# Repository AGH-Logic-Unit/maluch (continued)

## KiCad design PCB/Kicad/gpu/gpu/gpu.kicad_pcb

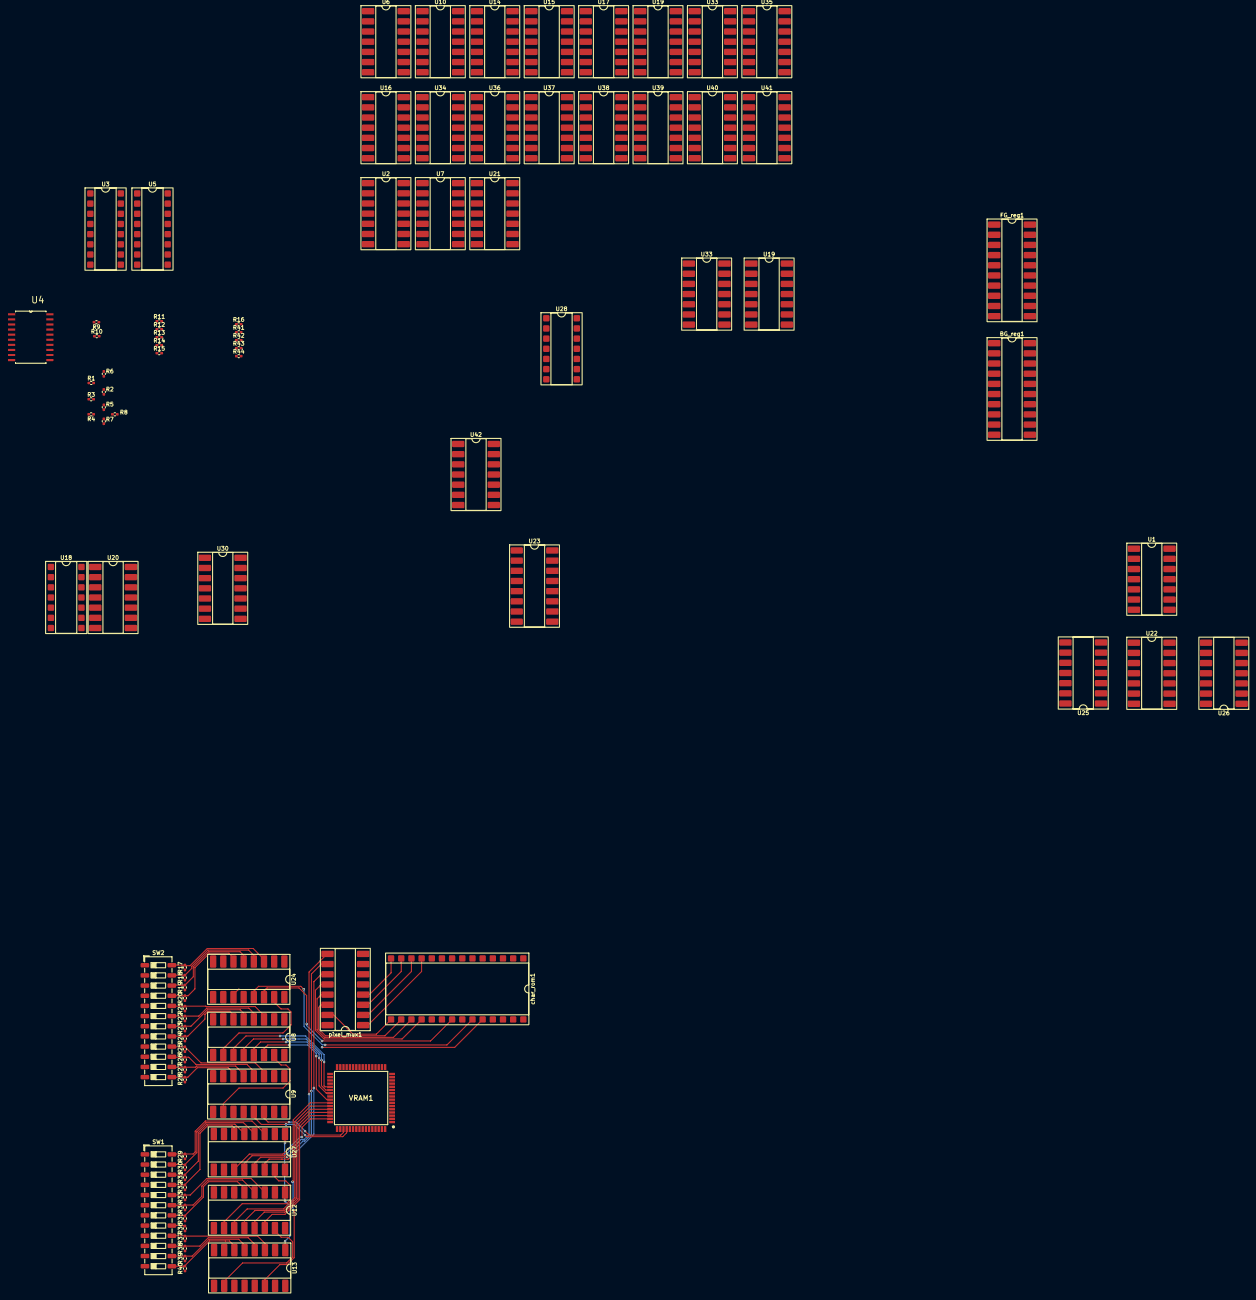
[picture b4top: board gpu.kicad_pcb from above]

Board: 2 copper layers, 91 parts (0 on the bottom side), 188 nets.

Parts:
BG_reg1: 74LS377; DIP-20_W8.89mm_SMDSocket_LongPads
FG_reg1: 74LS377; DIP-20_W8.89mm_SMDSocket_LongPads
R1, R3, R4, R6, R7, R9, R10, R11, R12, R15: 150; R_0402_1005Metric_Pad0.72x0.64mm_HandSolder
R2, R5, R8, R13, R14, R16, R43: 75; R_0402_1005Metric_Pad0.72x0.64mm_HandSolder
R17, R18, R19, R20, R21, R22, R23, R24, R25, R26, R27, R28, R29, R30, R31, R32, R33, R34, R35, R36, R37, R38, R39, R40: 10k; R_0402_1005Metric_Pad0.72x0.64mm_HandSolder
R41: 620; R_0402_1005Metric_Pad0.72x0.64mm_HandSolder
R42: 1k; R_0402_1005Metric_Pad0.72x0.64mm_HandSolder
R44: 390; R_0402_1005Metric_Pad0.72x0.64mm_HandSolder
SW1, SW2: SW_DIP_x12; SW_DIP_SPSTx12_Slide_6.7x32.04mm_W6.73mm_P2.54mm_LowProfile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
U1, U6, U10, U15, U16, U17, U22, U36, U39, U40: 74LS30; DIP-14_W8.89mm_SMDSocket_LongPads
U2, U7, U20, U21, U25, U26: 74LS04; DIP-14_W8.89mm_SMDSocket_LongPads
U3, U5: 74LS157; DIP-16_W7.62mm_SMDSocket_SmallPads
U4: 74HC574D.653; SOIC127P1032X265-20N
U8, U9, U12, U13, U24, U27: 74LS163; DIP-16_W8.89mm_SMDSocket_LongPads
U14, U34: 74LS00; DIP-14_W8.89mm_SMDSocket_LongPads
U18: 74LS08; DIP-14_W7.62mm_SMDSocket_SmallPads
U19, U19#2, U33, U33#2, U35, U37, U38, U41: 74LS32; DIP-14_W8.89mm_SMDSocket_LongPads
U23: 74LS175; DIP-16_W8.89mm_SMDSocket_LongPads
U28: 74LS11; DIP-14_W7.62mm_SMDSocket_SmallPads
U30, U42: 4075; DIP-14_W8.89mm_SMDSocket_LongPads
VRAM1: 71342LA20PFG8; QFP80P1600X1600X160-64N
char_rom1: AT28C64B-15PU; DIP-28_W15.24mm_SMDSocket_SmallPads
pixel_mux1: 74LS151; DIP-16_W8.89mm_SMDSocket_LongPads

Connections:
/HSYNC_OUT: U23.2 (Q0), U28.13
/Hcount0: U27.14 (Q0), pixel_mux1.11 (S0)
/Hcount1: U27.13 (Q1), pixel_mux1.10 (S1)
/Hcount2: U27.12 (Q2), pixel_mux1.9 (S2)
/Hcount3: U27.11 (Q3), VRAM1.47 (A0R)
/Hcount4: U12.14 (Q0), VRAM1.46 (A1R)
/Hcount5: U12.13 (Q1), VRAM1.45 (A2R)
/Hcount6: U12.12 (Q2), VRAM1.44 (A3R)
/Hcount7: U12.11 (Q3), VRAM1.43 (A4R)
/Hcount8: U13.14 (Q0), VRAM1.42 (A5R)
/I/O0: BG_reg1.3 (D0), FG_reg1.3 (D0)
/I/O1: BG_reg1.4 (D1), FG_reg1.4 (D1)
/I/O2: BG_reg1.7 (D2), FG_reg1.7 (D2)
/I/O3: BG_reg1.8 (D3), FG_reg1.8 (D3)
/I/O4: BG_reg1.13 (D4), FG_reg1.13 (D4)
/I/O5: BG_reg1.14 (D5), FG_reg1.14 (D5)
/I/O6: BG_reg1.17 (D6), FG_reg1.17 (D6)
/I/O7: BG_reg1.18 (D7), FG_reg1.18 (D7)
/I/O8: U22.1, U25.3
/I/O9: U1.2, U22.2
/Output/Blue0: R41.1, U4.12 (Q7)
/Output/Blue1: R42.1, U4.13 (Q6)
/Output/Bout: R43.2, R44.2
/Output/Green0: R1.1, U4.16 (Q3)
/Output/Green1: R3.1, U4.15 (Q4)
/Output/Green2: R4.1, U4.14 (Q5)
/Output/PixIn: U3.1 (S), U5.1 (S), pixel_mux1.5 (Z)
/Output/Red0: R9.1, U4.19 (Q0)
/Output/Red1: R10.1, U4.18 (Q1)
/Output/Red2: R11.1, U4.17 (Q2)
/VGA Synchronization/12bit Hcounter/nRST: U12.1 (~MR), U13.1 (~MR), U18.3, U27.1 (~MR)
/VGA Synchronization/12bit Vcounter/DSET0: R17.2, SW2.24, U24.3 (D0)
/VGA Synchronization/12bit Vcounter/DSET1: R18.2, SW2.23, U24.4 (D1)
/VGA Synchronization/12bit Vcounter/DSET2: R19.2, SW2.22, U24.5 (D2)
/VGA Synchronization/12bit Vcounter/DSET3: R20.2, SW2.21, U24.6 (D3)
/VGA Synchronization/12bit Vcounter/DSET4: R21.2, SW2.20, U8.3 (D0)
/VGA Synchronization/12bit Vcounter/DSET5: R22.2, SW2.19, U8.4 (D1)
/VGA Synchronization/12bit Vcounter/DSET6: R23.2, SW2.18, U8.5 (D2)
/VGA Synchronization/12bit Vcounter/DSET7: R24.2, SW2.17, U8.6 (D3)
/VGA Synchronization/12bit Vcounter/DSET8: R25.2, SW2.16, U9.3 (D0)
/VGA Synchronization/12bit Vcounter/DSET9: R26.2, SW2.15, U9.4 (D1)
/VGA Synchronization/12bit Vcounter/DSET10: R27.2, SW2.14, U9.5 (D2)
/VGA Synchronization/12bit Vcounter/DSET11: R28.2, SW2.13, U9.6 (D3)
/VGA Synchronization/12bit Vcounter/EN: U8.7 (CEP), U9.7 (CEP), U18.2, U20.3, U24.7 (CEP), U37.6
/VGA Synchronization/12bit Vcounter/nRST: U8.1 (~MR), U9.1 (~MR), U18.8, U24.1 (~MR)
/VGA Synchronization/HSET0: R29.2, SW1.24, U27.3 (D0)
/VGA Synchronization/HSET1: R30.2, SW1.23, U27.4 (D1)
/VGA Synchronization/HSET2: R31.2, SW1.22, U27.5 (D2)
/VGA Synchronization/HSET3: R32.2, SW1.21, U27.6 (D3)
/VGA Synchronization/HSET4: R33.2, SW1.20, U12.3 (D0)
/VGA Synchronization/HSET5: R34.2, SW1.19, U12.4 (D1)
/VGA Synchronization/HSET6: R35.2, SW1.18, U12.5 (D2)
/VGA Synchronization/HSET7: R36.2, SW1.17, U12.6 (D3)
/VGA Synchronization/HSET8: R37.2, SW1.16, U13.3 (D0)
/VGA Synchronization/HSET9: R38.2, SW1.15, U13.4 (D1)
/VGA Synchronization/HSET10: R39.2, SW1.14, U13.5 (D2)
/VGA Synchronization/HSET11: R40.2, SW1.13, U13.6 (D3)
/VGA Synchronization/HVis: U18.5, U23.7 (Q1), U28.10
/VGA Synchronization/Hctrl/COUNT0: U16.1, U36.1, U39.1, U40.1
/VGA Synchronization/Hctrl/COUNT1: U16.2, U36.2, U39.2, U40.2
/VGA Synchronization/Hctrl/COUNT2: U16.3, U36.3, U39.3, U40.3
/VGA Synchronization/Hctrl/COUNT3: U16.4, U36.4, U39.4, U40.4
/VGA Synchronization/Hctrl/COUNT4: U16.5, U21.1, U40.5
/VGA Synchronization/Hctrl/COUNT5: U21.3, U39.6, U40.6
/VGA Synchronization/Hctrl/COUNT6: U21.5, U39.11, U40.11
/VGA Synchronization/Hctrl/COUNT7: U21.9, U36.12, U39.12
/VGA Synchronization/Hctrl/COUNT8: U21.11, U34.1
/VGA Synchronization/Hctrl/COUNT9: U34.2, U34.5, U34.10, U34.13
/VGA Synchronization/Hctrl/HBeginPulse: U28.1, U37.3, U38.6
/VGA Synchronization/Hctrl/HEndPulse: U20.1, U28.2, U37.8
/VGA Synchronization/Hctrl/HVisEnd: U18.4, U37.11, U41.6
/VGA Synchronization/Hctrl/nCOUNT4: U21.2, U36.5, U39.5
/VGA Synchronization/Hctrl/nCOUNT5: U16.6, U21.4, U36.6
/VGA Synchronization/Hctrl/nCOUNT6: U16.11, U21.6, U36.11
/VGA Synchronization/Hctrl/nCOUNT7: U16.12, U21.8, U40.12
/VGA Synchronization/Hctrl/nCOUNT8: U21.10, U34.4, U34.9, U34.12
/VGA Synchronization/VVis: U18.13, U23.15 (Q3), U28.11
/VGA Synchronization/Vctrl/COUNT0: U6.1, U7.5, U10.1, U17.1
/VGA Synchronization/Vctrl/COUNT1: U6.2, U7.9, U10.2
/VGA Synchronization/Vctrl/COUNT2: U6.3, U7.13, U15.3, U17.3
/VGA Synchronization/Vctrl/COUNT3: U6.4, U7.11, U10.4, U15.4
/VGA Synchronization/Vctrl/COUNT4: U2.1, U6.5
/VGA Synchronization/Vctrl/COUNT5: U2.3, U10.6
/VGA Synchronization/Vctrl/COUNT6: U2.5, U6.11, U10.11
/VGA Synchronization/Vctrl/COUNT7: U2.9, U6.12, U10.12, U17.12
/VGA Synchronization/Vctrl/COUNT8: U2.11, U14.4, U14.9, U14.12
/VGA Synchronization/Vctrl/COUNT9: U2.13, U14.2
/VGA Synchronization/Vctrl/nCOUNT0: U7.6, U15.1
/VGA Synchronization/Vctrl/nCOUNT1: U7.8, U15.2, U17.2
/VGA Synchronization/Vctrl/nCOUNT2: U7.12, U10.3
/VGA Synchronization/Vctrl/nCOUNT3: U7.10, U17.4
/VGA Synchronization/Vctrl/nCOUNT4: U2.2, U10.5, U15.5, U17.5
/VGA Synchronization/Vctrl/nCOUNT5: U2.4, U6.6, U15.6, U17.6
/VGA Synchronization/Vctrl/nCOUNT6: U2.6, U15.11, U17.11
/VGA Synchronization/Vctrl/nCOUNT7: U2.8, U15.12
/VGA Synchronization/Vctrl/nCOUNT8: U2.10, U14.1
/VGA Synchronization/Vctrl/nCOUNT9: U2.12, U14.5, U14.10, U14.13
/VGA Synchronization/Vctrl/nVBeginPulse: U28.3, U33.6, U35.6
/VGA Synchronization/Vctrl/nVEndPulse: U7.1, U28.4, U33.8, U33#2.3
/VGA Synchronization/Vctrl/nVVisEnd: U18.12, U19.6, U33.11
/VGA Synchronization/Vctrl/nVcountEnd: U7.3, U18.10, U33.3, U33#2.6
/VSYNC_OUT: U23.10 (Q2), U28.5
/Vcount0: U24.14 (Q0), char_rom1.21 (A10)
/Vcount1: U24.13 (Q1), char_rom1.23 (A11)
/Vcount2: U24.12 (Q2), char_rom1.24 (A9)
/Vcount3: U24.11 (Q3), char_rom1.25 (A8)
/Vcount4: U8.14 (Q0), VRAM1.41 (A6R)
/Vcount5: U8.13 (Q1), VRAM1.39 (A7R)
/Vcount6: U8.12 (Q2), VRAM1.38 (A8R)
/Vcount7: U8.11 (Q3), VRAM1.37 (A9R)
/Vcount8: U9.14 (Q0), VRAM1.51 (A10R)
/Vcount9: U9.13 (Q1), VRAM1.52 (A11R)
/charRow0: char_rom1.14 (GND), pixel_mux1.4 (I0)
/charRow1: char_rom1.13 (I/O2), pixel_mux1.3 (I1)
/charRow2: char_rom1.12 (I/O1), pixel_mux1.2 (I2)
/charRow3: char_rom1.11 (I/O0), pixel_mux1.1 (I3)
/charRow4: char_rom1.15 (I/O3), pixel_mux1.15 (I4)
/charRow5: char_rom1.16 (I/O4), pixel_mux1.14 (I5)
/charRow6: char_rom1.17 (I/O5), pixel_mux1.13 (I6)
/charRow7: char_rom1.18 (I/O6), pixel_mux1.12 (I7)
/commands/nio8: U1.1, U25.4
/commands/nio10: U1.3, U22.3, U25.6
/commands/nio11: U1.4, U22.4, U25.8
/commands/nio12: U1.5, U22.5, U25.10
/commands/nio13: U1.6, U22.6, U25.12
/commands/nio14: U1.11, U22.11, U26.2
/commands/nio15: U1.12, U22.12, U26.4
/ioCLK: BG_reg1.11 (CP), FG_reg1.11 (CP)
/nRST: U18.1, U18.9, U21.13
/nVis: U3.15 (E), U5.15 (E)
/pCLK: U8.2 (CP), U9.2 (CP), U12.2 (CP), U13.2 (CP), U24.2 (CP), U27.2 (CP)
GND: BG_reg1.10 (GND), FG_reg1.10 (GND), R6.1, R7.2, R12.1, R15.2, R17.1, R18.1, R19.1, R20.1, R21.1, R22.1, R23.1, R24.1, R25.1, R26.1, R27.1, R28.1, R29.1, R30.1, R31.1, R32.1, R33.1, R34.1, R35.1, R36.1, R37.1, R38.1, R39.1, R40.1, U1.7 (GND), U2.7 (GND), U3.8 (GND), U4.1 (~OE), U4.10 (GND), U5.8 (GND), U6.7 (GND), U7.7 (GND), U8.8 (GND), U9.8 (GND), U10.7 (GND), U12.8 (GND), U13.8 (GND), U14.7 (GND), U15.7 (GND), U16.7 (GND), U17.7 (GND), U18.7 (GND), U19.7 (GND), U19#2.7 (GND), U20.7 (GND), U21.7 (GND), U22.7 (GND), U23.8 (GND), U24.8 (GND), U25.7 (GND), U26.7 (GND), U27.8 (GND), U28.7 (GND), U30.7 (VSS), U36.7 (GND), U37.7 (GND), U39.7 (GND), U40.7 (GND), VRAM1.25 (GND), VRAM1.55 (~CER), VRAM1.59 (R/~WL), char_rom1.2 (A12), char_rom1.20 (~CE), char_rom1.22 (~OE), pixel_mux1.7 (~E), pixel_mux1.8 (GND)
unnamed: BG_reg1.1 (~E), U19#2.6
unnamed: FG_reg1.1 (~E), U19#2.3
unnamed: R1.2, R2.2, R6.2
unnamed: R2.1, R3.2, R5.2
unnamed: R4.2, R5.1, R7.1, R8.2
unnamed: R10.2, R13.1, R14.2
unnamed: R11.2, R14.1, R15.1, R16.2
unnamed: R9.2, R12.2, R13.2
unnamed: R41.2, R43.1
unnamed: R42.2, R44.1
unnamed: U1.8, U19#2.2
unnamed: U3.4 (Za), U4.6 (D4)
unnamed: U3.7 (Zb), U4.7 (D5)
unnamed: U3.9 (Zc), U4.8 (D6)
unnamed: U3.12 (Zd), U4.9 (D7)
unnamed: U4.2 (D0), U5.7 (Zb)
unnamed: U4.3 (D1), U5.4 (Za)
unnamed: U4.4 (D2), U5.9 (Zc)
unnamed: U4.5 (D3), U5.12 (Zd)
unnamed: U8.15 (TC), U9.10 (CET)
unnamed: U10.8, U33.9, U33#2.1
unnamed: U12.10 (CET), U27.15 (TC)
unnamed: U12.15 (TC), U13.10 (CET)
unnamed: U14.3, U33.2, U33#2.5
unnamed: U14.6, U33.5, U35.5
unnamed: U14.8, U33.10, U33#2.2
unnamed: U14.11, U19.5, U33.13
unnamed: U15.8, U33.1, U33#2.4
unnamed: U16.8, U37.4
unnamed: U17.8, U33.4, U35.4
unnamed: U18.6, U30.5
unnamed: U18.11, U42.8
unnamed: U19#2.1, U19#2.4, U25.2
unnamed: U19#2.5, U22.8
unnamed: U20.2, U30.1
unnamed: U20.4, U30.3
unnamed: U20.5, U28.8
unnamed: U21.12, U30.2, U30.4, U30.12, U42.2
unnamed: U23.4 (D0), U30.9
unnamed: U23.5 (D1), U30.6
unnamed: U23.12 (D2), U30.10
unnamed: U23.13 (D3), U42.9
unnamed: U8.10 (CET), U24.15 (TC)
unnamed: U28.6, U30.13
unnamed: U28.12, U30.8
unnamed: U7.2, U30.11
unnamed: U6.8, U33.12
unnamed: U34.3, U37.5
unnamed: U34.6, U37.2, U38.5
unnamed: U34.8, U37.10
unnamed: U34.11, U37.13, U41.5
unnamed: U36.8, U37.1, U38.4
unnamed: U37.9, U39.8
unnamed: U37.12, U40.8
unnamed: U7.4, U42.1
VCC: BG_reg1.20 (VCC), FG_reg1.20 (VCC), SW1.1, SW1.2, SW1.3, SW1.4, SW1.5, SW1.6, SW1.7, SW1.8, SW1.9, SW1.10, SW1.11, SW1.12, SW2.1, SW2.2, SW2.3, SW2.4, SW2.5, SW2.6, SW2.7, SW2.8, SW2.9, SW2.10, SW2.11, SW2.12, U1.14 (VCC), U2.14 (VCC), U3.16 (VCC), U4.20 (VCC), U5.16 (VCC), U6.14 (VCC), U7.14 (VCC), U8.9 (~PE), U8.16 (VCC), U9.9 (~PE), U9.16 (VCC), U10.14 (VCC), U12.7 (CEP), U12.9 (~PE), U12.16 (VCC), U13.7 (CEP), U13.9 (~PE), U13.16 (VCC), U14.14 (VCC), U15.14 (VCC), U16.14 (VCC), U17.14 (VCC), U18.14 (VCC), U19.14 (VCC), U19#2.14 (VCC), U20.14 (VCC), U21.14 (VCC), U22.14 (VCC), U23.16 (VCC), U24.9 (~PE), U24.10 (CET), U24.16 (VCC), U25.14 (VCC), U26.14 (VCC), U27.7 (CEP), U27.9 (~PE), U27.10 (CET), U27.16 (VCC), U28.9, U28.14 (VCC), U30.14 (VDD), U36.14 (VCC), U37.14 (VCC), U39.14 (VCC), U40.14 (VCC), VRAM1.1 (~OEL), VRAM1.53 (~SEM_R), VRAM1.54 (R/~WR), VRAM1.57 (VCC), VRAM1.60 (~SEML), char_rom1.27 (~WE), char_rom1.28 (VCC), pixel_mux1.16 (VCC)

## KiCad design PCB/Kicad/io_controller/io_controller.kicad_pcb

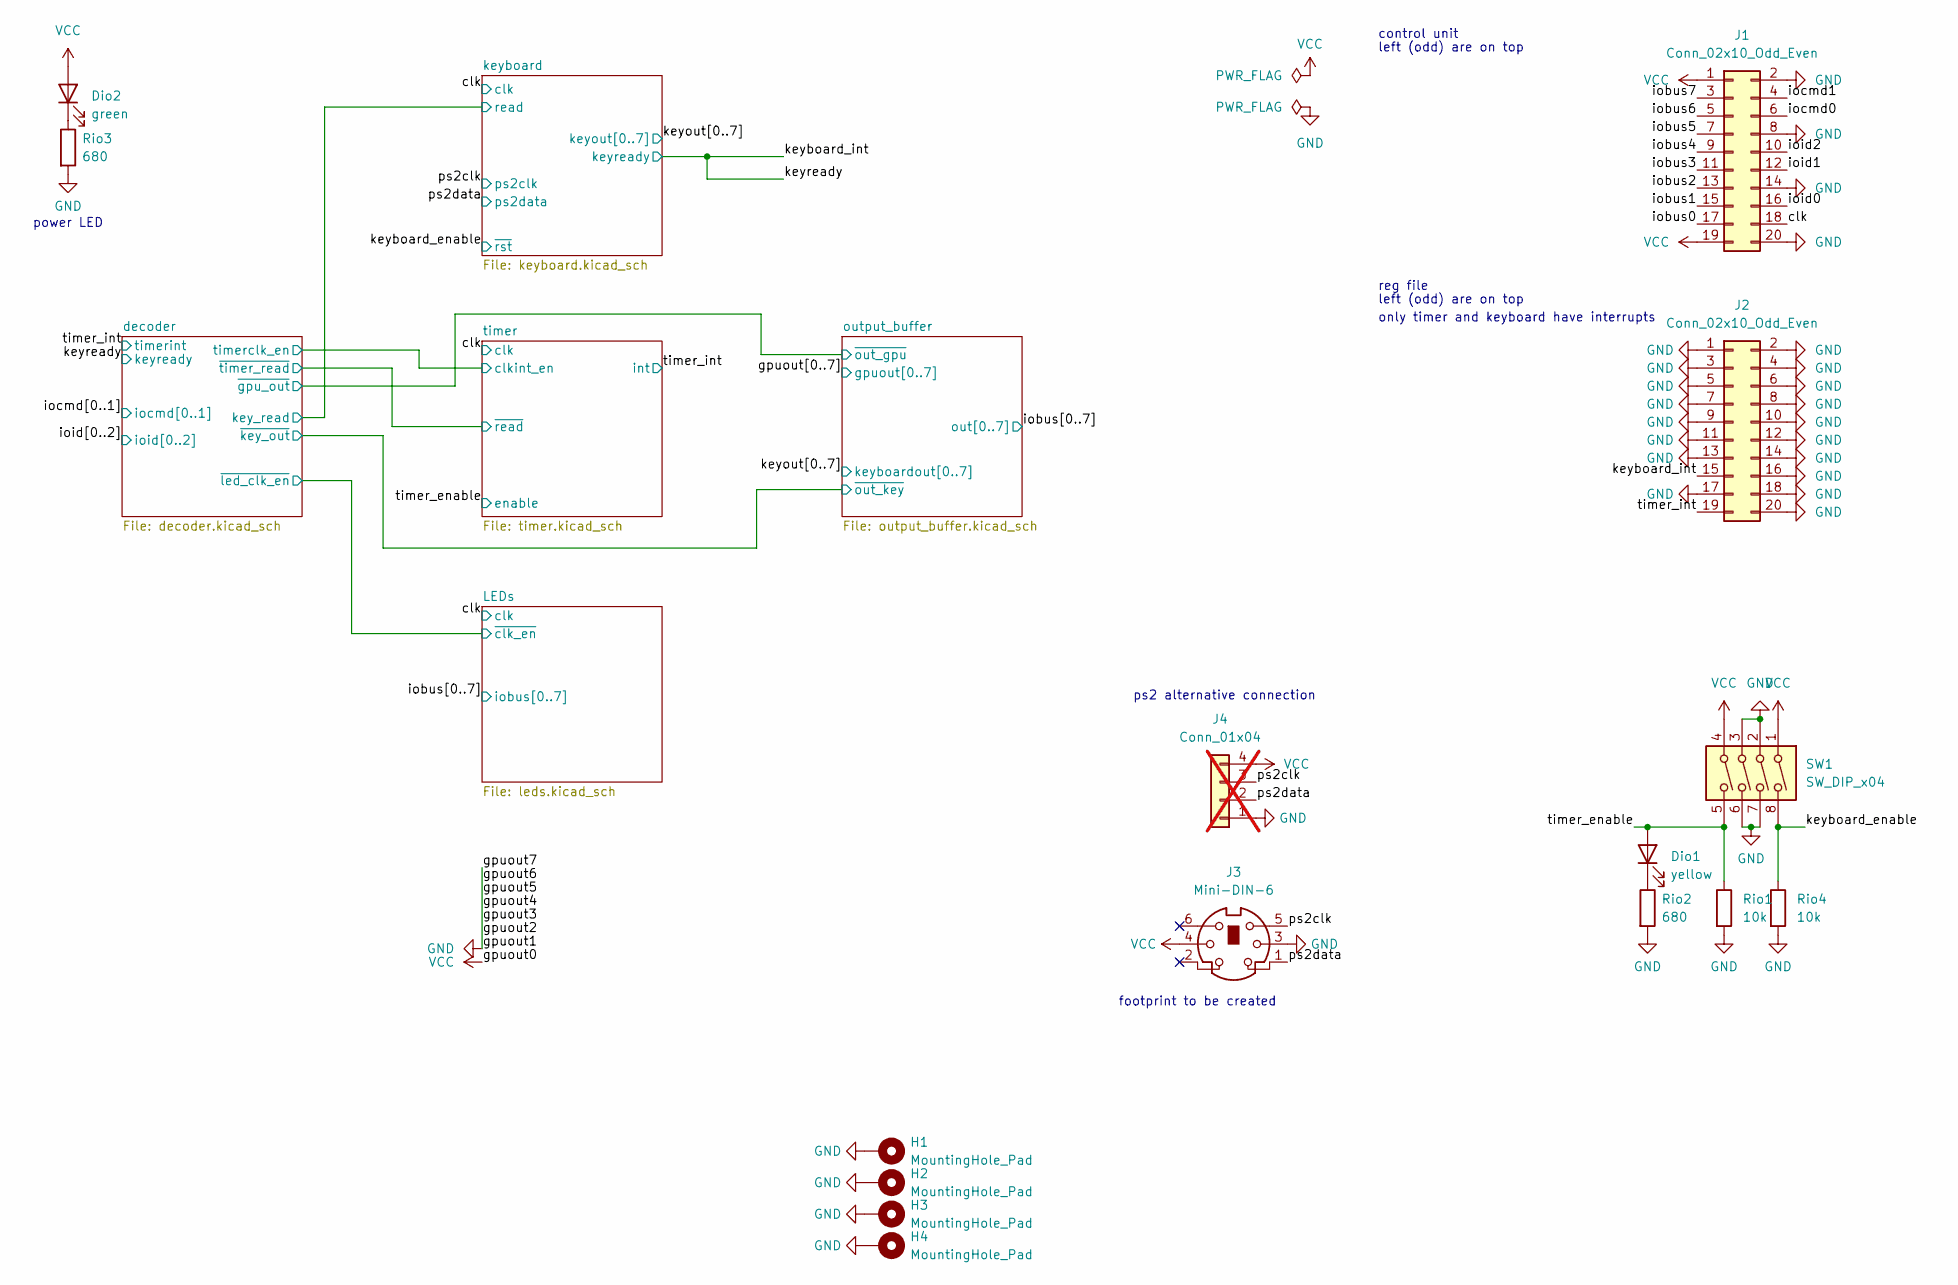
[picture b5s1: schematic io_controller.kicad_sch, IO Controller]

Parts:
Dio1: yellow; D_0603_1608Metric
Dio2: green; D_0603_1608Metric
H1, H2, H3, H4: MountingHole_Pad; MountingHole_2.2mm_M2_DIN965_Pad
J1, J2: Conn_02x10_Odd_Even; PinHeader_2x10_P2.54mm_Horizontal
J3: Mini-DIN-6; MiniDin6_PS2
J4: Conn_01x04; PinHeader_1x04_P2.54mm_Vertical; not fitted
Rio1, Rio4: 10k; R_0402_1005Metric
Rio2, Rio3: 680; R_0402_1005Metric
SW1: SW_DIP_x04; SW_DIP_SPSTx04_Slide_6.7x11.72mm_W7.62mm_P2.54mm_LowProfile

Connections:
/clk: J1.18; also elsewhere on the board
/iobus0: J1.17; also elsewhere on the board
/iobus1: J1.15; also elsewhere on the board
/iobus2: J1.13; also elsewhere on the board
/iobus3: J1.11; also elsewhere on the board
/iobus4: J1.9; also elsewhere on the board
/iobus5: J1.7; also elsewhere on the board
/iobus6: J1.5; also elsewhere on the board
/iobus7: J1.3; also elsewhere on the board
/iocmd0: J1.6; also elsewhere on the board
/iocmd1: J1.4; also elsewhere on the board
/ioid0: J1.16; also elsewhere on the board
/ioid1: J1.12; also elsewhere on the board
/ioid2: J1.10; also elsewhere on the board
/keyboard_enable: Rio4.1, SW1.8; also elsewhere on the board
/keyboard_int: J2.15; also elsewhere on the board
/ps2clk: J3.5, J4.3; also elsewhere on the board
/ps2data: J3.1, J4.2; also elsewhere on the board
/timer_enable: Dio1.2 (A), Rio1.1, SW1.5; also elsewhere on the board
/timer_int: J2.19; also elsewhere on the board
GND: H1.1 (1_1), H2.1 (1_1), H3.1 (1_1), H4.1 (1_1), J1.2, J1.8, J1.14, J1.20, J2.1, J2.2, J2.3, J2.4, J2.5, J2.6, J2.7, J2.8, J2.9, J2.10, J2.11, J2.12, J2.13, J2.14, J2.16, J2.17, J2.18, J2.20, J3.3, J4.1, Rio1.2, Rio2.2, Rio3.2, Rio4.2, SW1.2, SW1.3, SW1.6, SW1.7; also elsewhere on the board
unnamed: Dio1.1 (K), Rio2.1
unnamed: Dio2.1 (K), Rio3.1
VCC: Dio2.2 (A), J1.1, J1.19, J3.4, J4.4, SW1.1, SW1.4; also elsewhere on the board

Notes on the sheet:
left (odd) are on top
power LED
ps2 alternative connection
control unit
reg file
footprint to be created
only timer and keyboard have interrupts

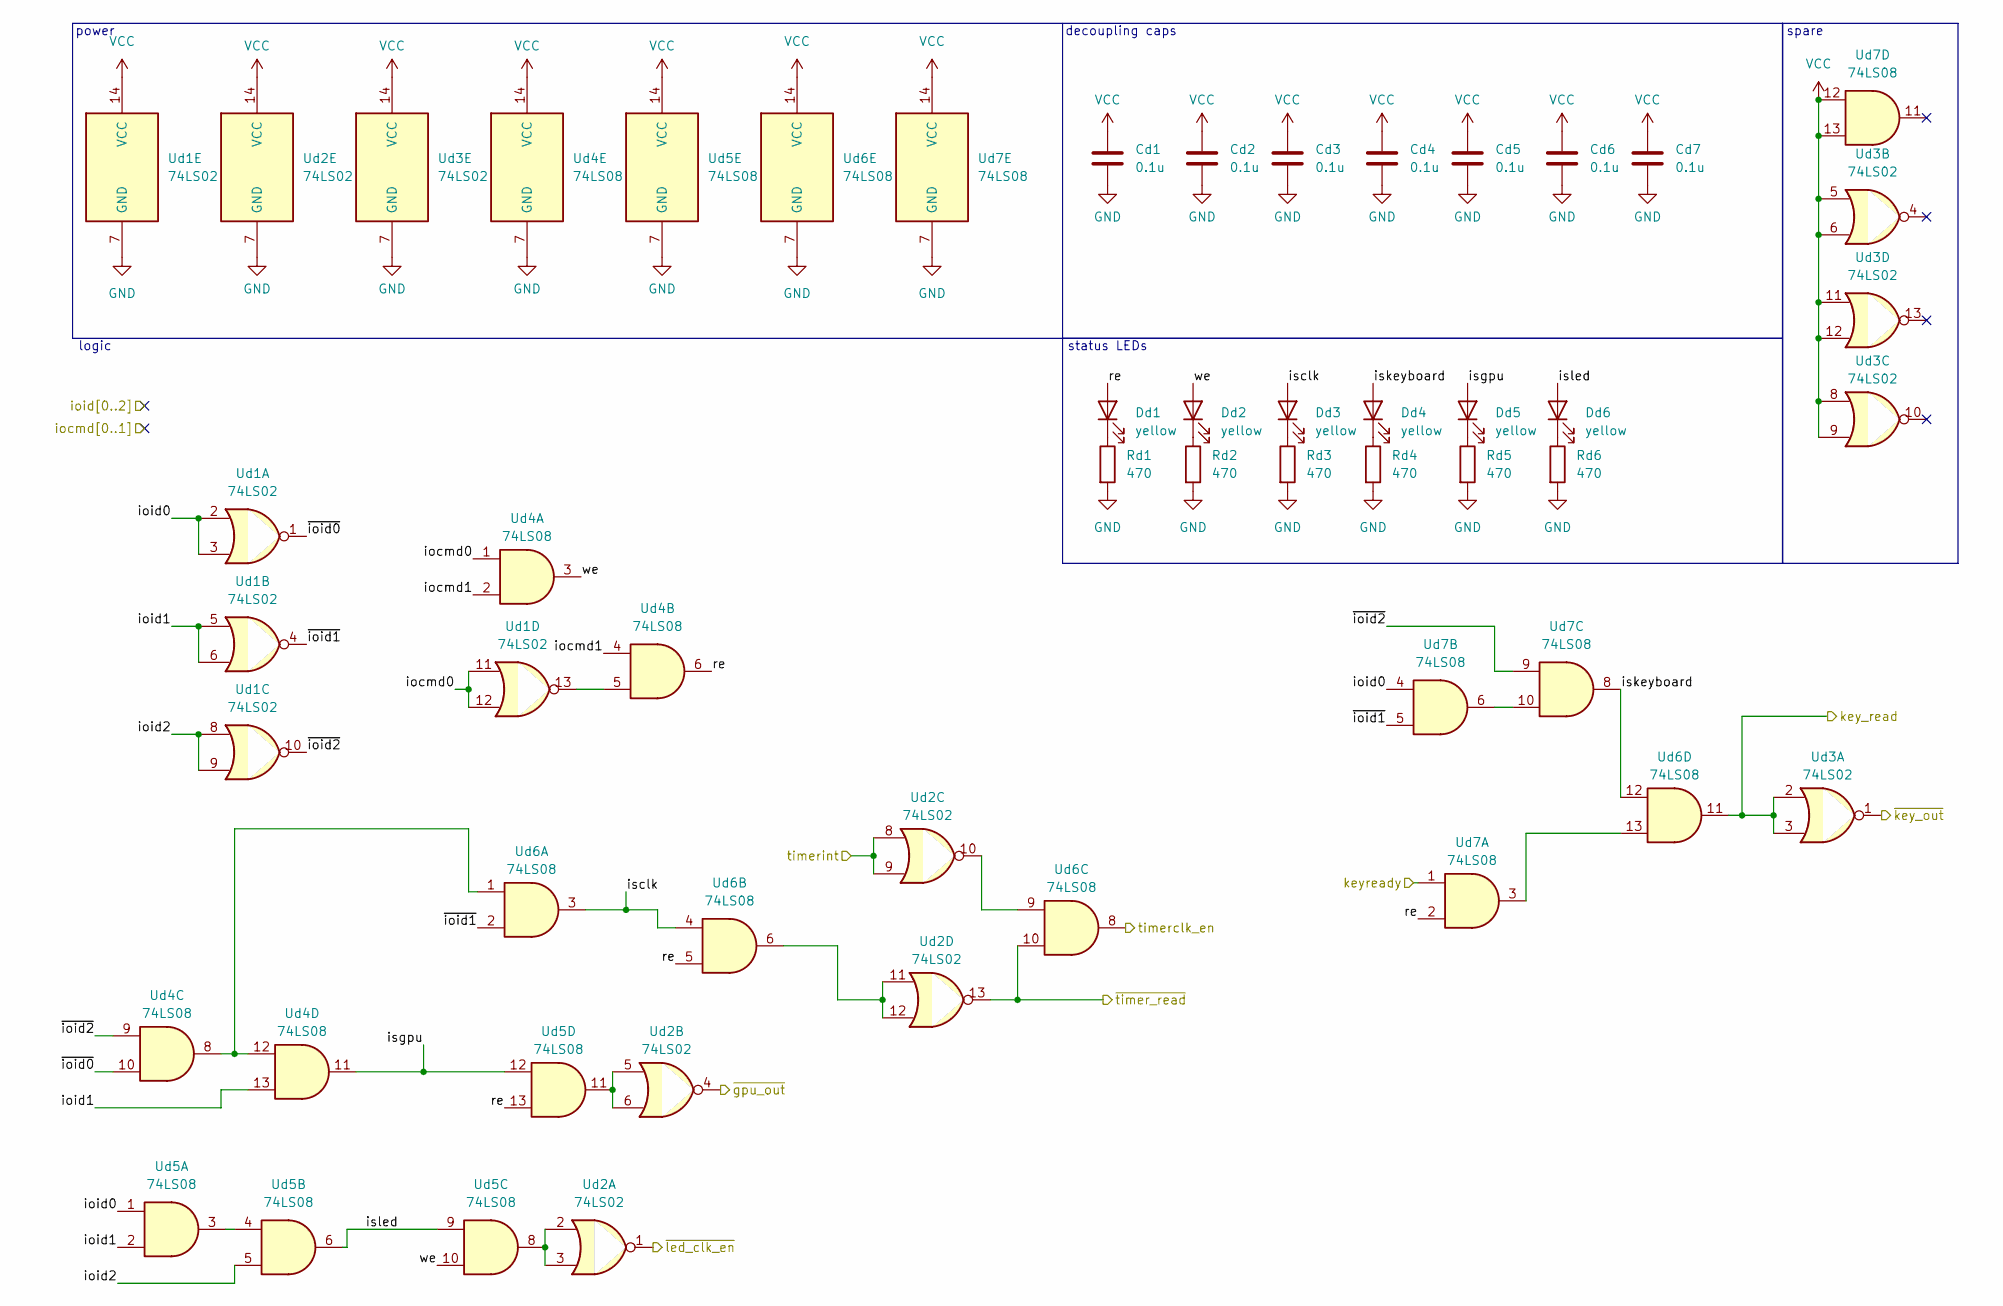
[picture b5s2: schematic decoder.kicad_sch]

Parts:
Cd1, Cd2, Cd3, Cd4, Cd5, Cd6, Cd7: 0.1u; C_0402_1005Metric
Dd1, Dd2, Dd3, Dd4, Dd5, Dd6: yellow; LED_0603_1608Metric
Rd1, Rd2, Rd3, Rd4, Rd5, Rd6: 470; R_0402_1005Metric
Ud1, Ud2, Ud3: 74LS02; SO-14_3.9x8.65mm_P1.27mm
Ud4, Ud5, Ud6, Ud7: 74LS08; SOIC-14_3.9x8.7mm_P1.27mm

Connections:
/LEDs/~clk_en: Ud2.1; also elsewhere on the board
/decoder/isclk: Dd3.2 (A), Ud6.3, Ud6.4
/decoder/isgpu: Dd5.2 (A), Ud4.11, Ud5.12
/decoder/iskeyboard: Dd4.2 (A), Ud6.12, Ud7.8
/decoder/isled: Dd6.2 (A), Ud5.6, Ud5.9
/decoder/key_read: Ud3.2, Ud3.3, Ud6.11; also elsewhere on the board
/decoder/re: Dd1.2 (A), Ud4.6, Ud5.13, Ud6.5, Ud7.2
/decoder/timerclk_en: Ud6.8; also elsewhere on the board
/decoder/we: Dd2.2 (A), Ud4.3, Ud5.10
/decoder/~gpu_out: Ud2.4; also elsewhere on the board
/decoder/~ioid0: Ud1.1, Ud4.10
/decoder/~ioid1: Ud1.4, Ud6.2, Ud7.5
/decoder/~ioid2: Ud1.10, Ud4.9, Ud7.9
/decoder/~key_out: Ud3.1; also elsewhere on the board
/decoder/~timer_read: Ud2.13, Ud6.10; also elsewhere on the board
/iocmd0: Ud1.11, Ud1.12, Ud4.1; also elsewhere on the board
/iocmd1: Ud4.2, Ud4.4; also elsewhere on the board
/ioid0: Ud1.2, Ud1.3, Ud5.1, Ud7.4; also elsewhere on the board
/ioid1: Ud1.5, Ud1.6, Ud4.13, Ud5.2; also elsewhere on the board
/ioid2: Ud1.8, Ud1.9, Ud5.5; also elsewhere on the board
/keyboard_int: Ud7.1; also elsewhere on the board
/timer_int: Ud2.8, Ud2.9; also elsewhere on the board
GND: Cd1.2, Cd2.2, Cd3.2, Cd4.2, Cd5.2, Cd6.2, Cd7.2, Rd1.2, Rd2.2, Rd3.2, Rd4.2, Rd5.2, Rd6.2, Ud1.7 (GND), Ud2.7 (GND), Ud3.7 (GND), Ud4.7 (GND), Ud5.7 (GND), Ud6.7 (GND), Ud7.7 (GND); also elsewhere on the board
unnamed: Dd1.1 (K), Rd1.1
unnamed: Dd2.1 (K), Rd2.1
unnamed: Dd3.1 (K), Rd3.1
unnamed: Dd4.1 (K), Rd4.1
unnamed: Dd5.1 (K), Rd5.1
unnamed: Dd6.1 (K), Rd6.1
unnamed: Ud1.13, Ud4.5
unnamed: Ud2.2, Ud2.3, Ud5.8
unnamed: Ud2.5, Ud2.6, Ud5.11
unnamed: Ud2.10, Ud6.9
unnamed: Ud2.11, Ud2.12, Ud6.6
unnamed: Ud4.8, Ud4.12, Ud6.1
unnamed: Ud5.3, Ud5.4
unnamed: Ud6.13, Ud7.3
unnamed: Ud7.6, Ud7.10
VCC: Cd1.1, Cd2.1, Cd3.1, Cd4.1, Cd5.1, Cd6.1, Cd7.1, Ud1.14 (VCC), Ud2.14 (VCC), Ud3.5, Ud3.6, Ud3.8, Ud3.9, Ud3.11, Ud3.12, Ud3.14 (VCC), Ud4.14 (VCC), Ud5.14 (VCC), Ud6.14 (VCC), Ud7.12, Ud7.13, Ud7.14 (VCC); also elsewhere on the board

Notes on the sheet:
logic
status LEDs
spare
decoupling caps
power

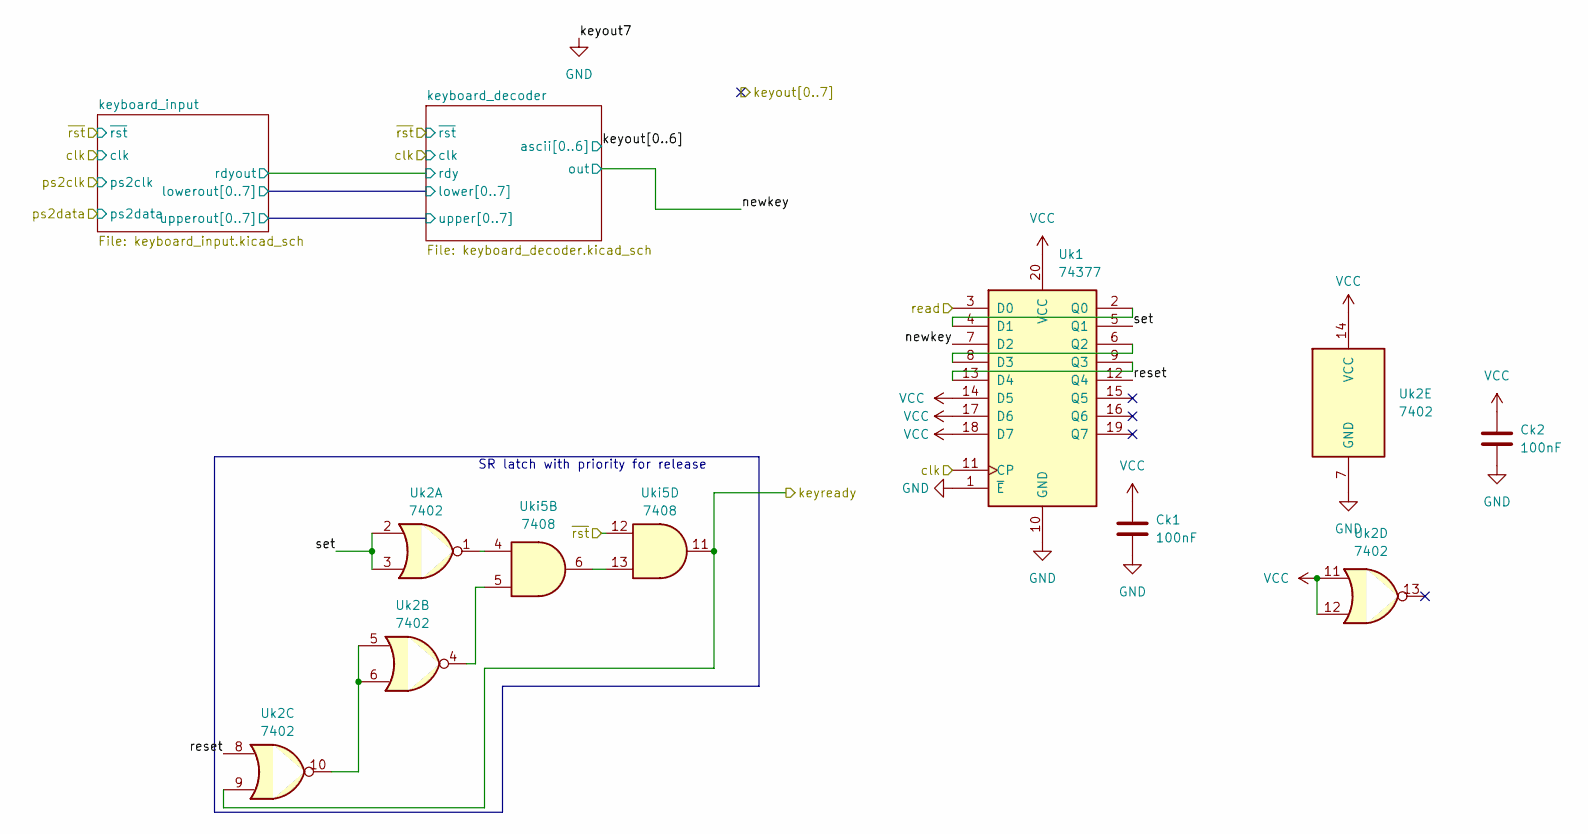
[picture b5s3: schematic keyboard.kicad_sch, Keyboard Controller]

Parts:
Ck1, Ck2: 100nF; C_0402_1005Metric
Uk1: 74377; SSOP-20_5.3x7.2mm_P0.65mm
Uk2: 7402; SOIC-14_3.9x8.7mm_P1.27mm
Uki5: 7408; SO-14_3.9x8.65mm_P1.27mm

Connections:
/clk: Uk1.11 (CP); also elsewhere on the board
/decoder/key_read: Uk1.3 (D0); also elsewhere on the board
/keyboard/newkey: Uk1.7 (D2); also elsewhere on the board
/keyboard/reset: Uk1.12 (Q4), Uk2.8
/keyboard/set: Uk1.5 (Q1), Uk2.2, Uk2.3
/keyboard_enable: Uki5.12; also elsewhere on the board
/keyboard_int: Uk2.9, Uki5.11; also elsewhere on the board
GND: Ck1.2, Ck2.2, Uk1.1 (~E), Uk1.10 (GND), Uk2.7 (GND); also elsewhere on the board
unnamed: Uk1.2 (Q0), Uk1.4 (D1)
unnamed: Uk1.6 (Q2), Uk1.8 (D3)
unnamed: Uk1.9 (Q3), Uk1.13 (D4)
unnamed: Uk2.1, Uki5.4
unnamed: Uk2.4, Uki5.5
unnamed: Uk2.5, Uk2.6, Uk2.10
unnamed: Uki5.6, Uki5.13
VCC: Ck1.1, Ck2.1, Uk1.14 (D5), Uk1.17 (D6), Uk1.18 (D7), Uk1.20 (VCC), Uk2.11, Uk2.12, Uk2.14 (VCC); also elsewhere on the board

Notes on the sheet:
SR latch with priority for release

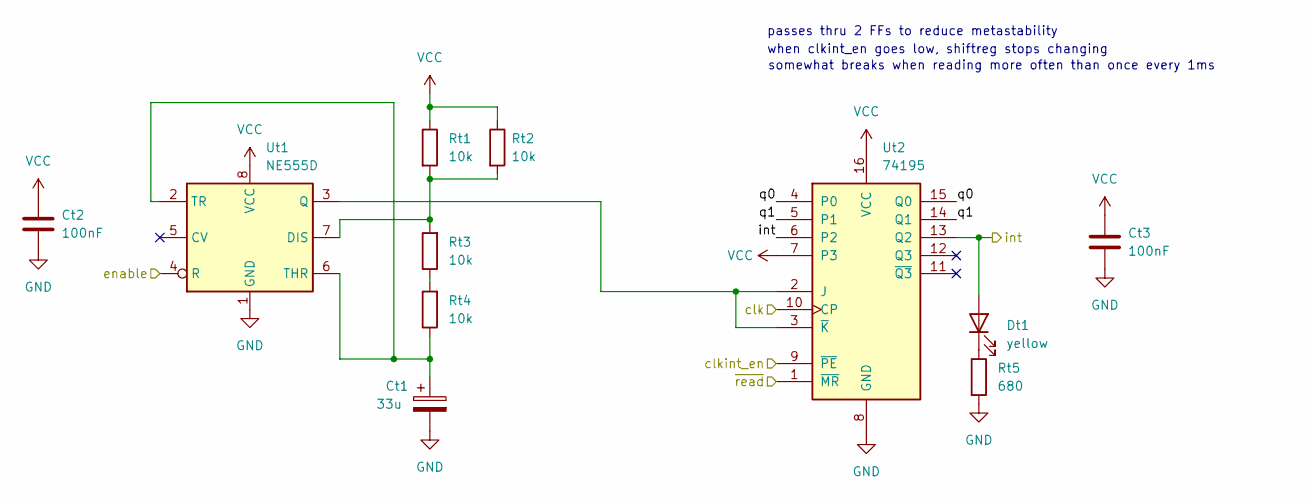
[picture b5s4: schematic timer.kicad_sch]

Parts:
Ct1: 33u; C_1206_3216Metric
Ct2, Ct3: 100nF; C_0402_1005Metric
Dt1: yellow; LED_0603_1608Metric
Rt1, Rt2, Rt3, Rt4: 10k; R_0402_1005Metric
Rt5: 680; R_0402_1005Metric
Ut1: NE555D; SOIC-8_3.9x4.9mm_P1.27mm
Ut2: 74195; SOIC-16_3.9x9.9mm_P1.27mm

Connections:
/clk: Ut2.10 (CP); also elsewhere on the board
/decoder/timerclk_en: Ut2.9 (~PE); also elsewhere on the board
/decoder/~timer_read: Ut2.1 (~MR); also elsewhere on the board
/timer/q0: Ut2.4 (P0), Ut2.15 (Q0)
/timer/q1: Ut2.5 (P1), Ut2.14 (Q1)
/timer_enable: Ut1.4 (R); also elsewhere on the board
/timer_int: Dt1.2 (A), Ut2.6 (P2), Ut2.13 (Q2); also elsewhere on the board
GND: Ct1.2, Ct2.2, Ct3.2, Rt5.2, Ut1.1 (GND), Ut2.8 (GND); also elsewhere on the board
unnamed: Dt1.1 (K), Rt5.1
unnamed: Rt3.1, Rt4.2
unnamed: Rt1.2, Rt2.2, Rt3.2, Ut1.7 (DIS)
unnamed: Ut1.3 (Q), Ut2.2 (J), Ut2.3 (~K)
unnamed: Ct1.1, Rt4.1, Ut1.2 (TR), Ut1.6 (THR)
VCC: Ct2.1, Ct3.1, Rt1.1, Rt2.1, Ut1.8 (VCC), Ut2.7 (P3), Ut2.16 (VCC); also elsewhere on the board

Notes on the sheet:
passes thru 2 FFs to reduce metastability
somewhat breaks when reading more often than once every 1ms
when clkint_en goes low, shiftreg stops changing

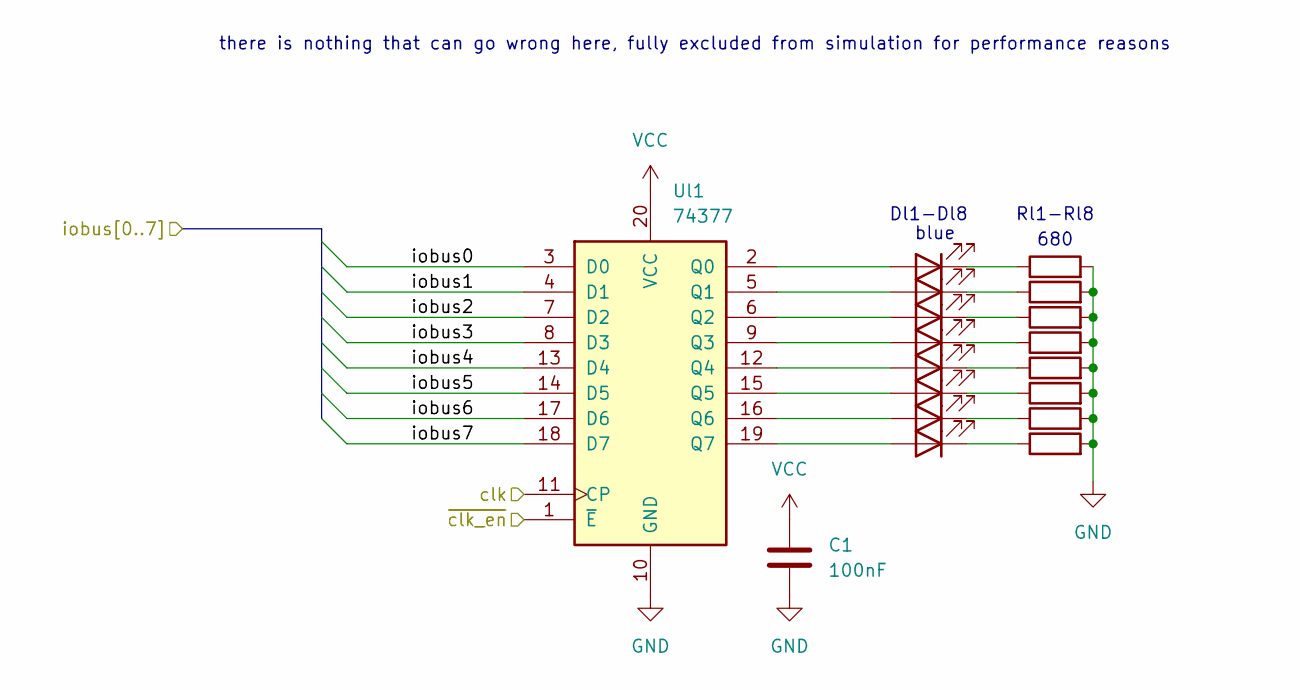
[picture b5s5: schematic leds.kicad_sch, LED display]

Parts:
C1: 100nF; C_0402_1005Metric
Dl1, Dl2, Dl3, Dl4, Dl5, Dl6, Dl7, Dl8: blue; LED_0603_1608Metric
Rl1, Rl2, Rl3, Rl4, Rl5, Rl6, Rl7, Rl8: 680; R_0402_1005Metric
Ul1: 74377; SSOP-20_5.3x7.2mm_P0.65mm

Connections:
/LEDs/~clk_en: Ul1.1 (~E); also elsewhere on the board
/clk: Ul1.11 (CP); also elsewhere on the board
/iobus0: Ul1.3 (D0); also elsewhere on the board
/iobus1: Ul1.4 (D1); also elsewhere on the board
/iobus2: Ul1.7 (D2); also elsewhere on the board
/iobus3: Ul1.8 (D3); also elsewhere on the board
/iobus4: Ul1.13 (D4); also elsewhere on the board
/iobus5: Ul1.14 (D5); also elsewhere on the board
/iobus6: Ul1.17 (D6); also elsewhere on the board
/iobus7: Ul1.18 (D7); also elsewhere on the board
GND: C1.1, Rl1.2, Rl2.2, Rl3.2, Rl4.2, Rl5.2, Rl6.2, Rl7.2, Rl8.2, Ul1.10 (GND); also elsewhere on the board
unnamed: Dl1.2 (A), Ul1.2 (Q0)
unnamed: Dl1.1 (K), Rl1.1
unnamed: Dl2.2 (A), Ul1.5 (Q1)
unnamed: Dl2.1 (K), Rl2.1
unnamed: Dl3.2 (A), Ul1.6 (Q2)
unnamed: Dl3.1 (K), Rl3.1
unnamed: Dl4.2 (A), Ul1.9 (Q3)
unnamed: Dl4.1 (K), Rl4.1
unnamed: Dl5.2 (A), Ul1.12 (Q4)
unnamed: Dl5.1 (K), Rl5.1
unnamed: Dl6.2 (A), Ul1.15 (Q5)
unnamed: Dl6.1 (K), Rl6.1
unnamed: Dl7.2 (A), Ul1.16 (Q6)
unnamed: Dl7.1 (K), Rl7.1
unnamed: Dl8.2 (A), Ul1.19 (Q7)
unnamed: Dl8.1 (K), Rl8.1
VCC: C1.2, Ul1.20 (VCC); also elsewhere on the board

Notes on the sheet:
Dl1-Dl8
blue
there is nothing that can go wrong here, fully excluded from simulation for performance reasons
680
Rl1-Rl8
